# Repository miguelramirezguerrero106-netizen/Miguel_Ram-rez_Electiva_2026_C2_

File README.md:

# Miguel_Ram-rez_Electiva_2026_C2_
Entrega de trabajos para la asignatura de Electiva C2-2026

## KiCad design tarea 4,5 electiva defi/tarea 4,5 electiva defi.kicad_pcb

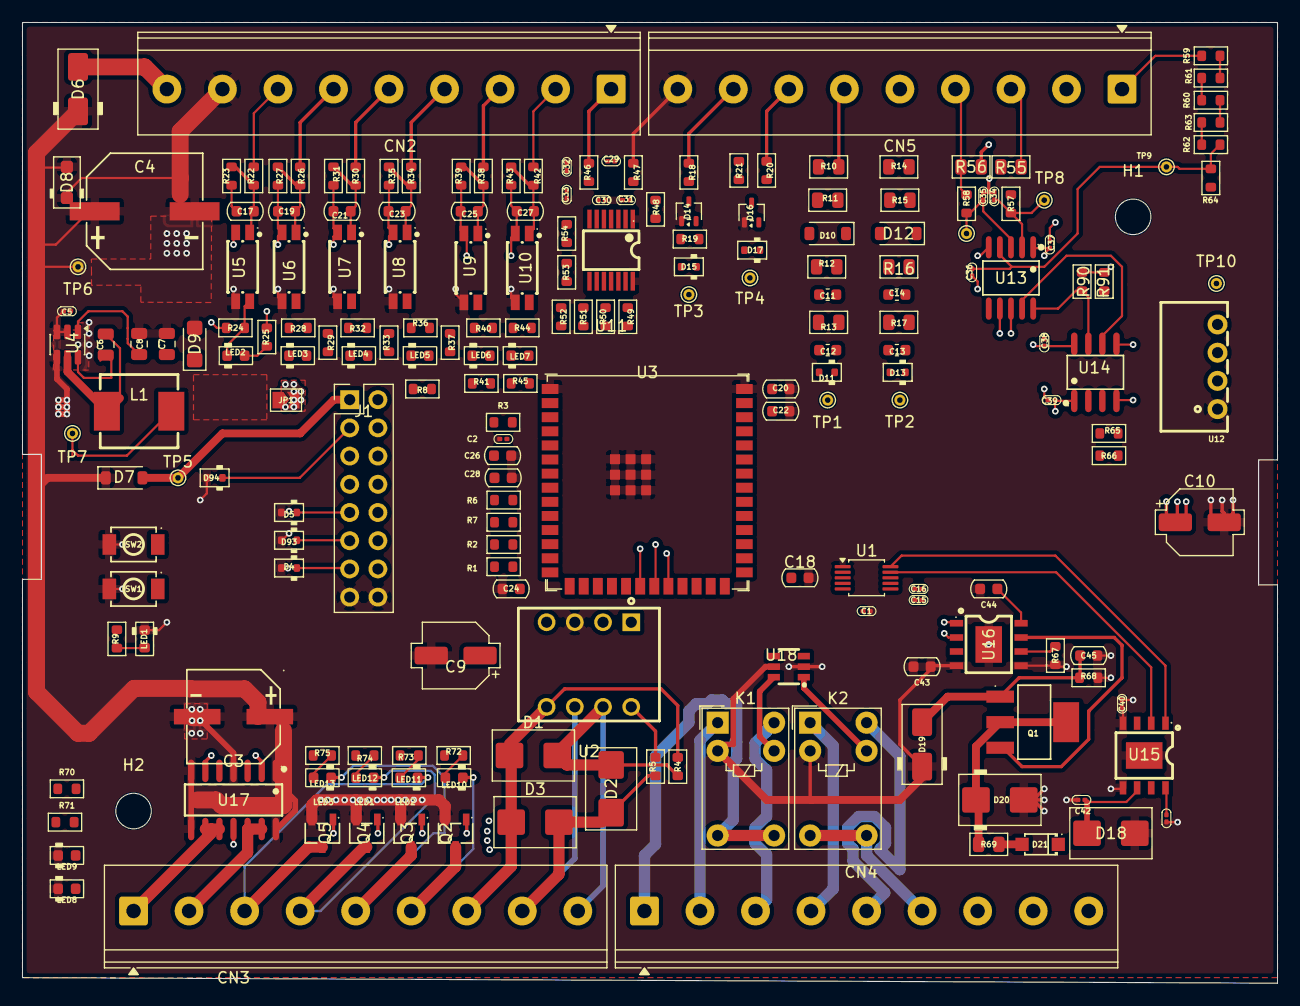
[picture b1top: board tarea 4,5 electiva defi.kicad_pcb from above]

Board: 4 copper layers, 113.0 x 86.5 mm, 205 parts (0 on the bottom side), 120 nets.

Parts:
C1, C2, C15, C16, C32, C33, C37, C38, C39: 100NF; C_0201_0603Metric
C3: 100uF; CAP-SMD_BD8.0-L8.3-W8.3-FD
C4: 220uF; CAP-SMD_BD10.0-L10.3-W10.3-LS11.3-FD
C5: 10uF; C_0201_0603Metric
C6: 100NF; C_0805_2012Metric
C7, C8: 22uF; C_0805_2012Metric
C9, C10: 47uF; CP_Elec_5x3
C11, C13: 100NF; C_0603_1608Metric
C12, C14: 47PF; C_0603_1608Metric
C17, C19, C21, C23, C25, C27: 2.2NF; C_0603_1608Metric
C18, C20, C22, C24, C26, C28: 1NF; C_0603_1608Metric
C29, C30: 0.01UF; C_0201_0603Metric
C31: 0.01; C_0201_0603Metric
C34, C35: 33NF; C_0201_0603Metric
C36: 68NF; C_0201_0603Metric
C40, C41, C42: C_0201; C_0201_0603Metric
C43, C44: C_0603; C_0603_1608Metric
C45: 1uF; C_0603_1608Metric
CN2, CN3, CN4, CN5: DB128V-5.08-9P-GN-S; TerminalBlock_Phoenix_PT-1,5-9-5.0-H_1x09_P5.00mm_Horizontal
D1, D3: SMBJ6.5CA; D_SMB_TVS
D2, D18: SMBJ12CA; D_SMB_TVS
D4, D5, D93, D94: ESD5Z3.3T; D_SOD-523
D6: MBRA340T; D_SMA
D7, D10, D12: 1N5819HW-7-F; D_SOD-123
D8: SMF24CA; D_SOD-123F
D9: SMF3.3; D_SMF
D11, D13, D15, D17: PESD5Z3.3; D_SOD-523
D14, D16: BAT54SW; SOT-323_SC-70
D19: SMAJ12A; D_SMA
D20: SMBJ28A; D_SMB
D21: DSK120_C22466355; SOD-123FL_L2.7-W1.8-LS3.8-RD
H1, H2: MountingHole; MountingHole_3.2mm_M3
J1: Conn_02x08_Odd_Even; PinHeader_2x08_P2.54mm_Vertical
JP1: SolderJumper_2_Open; SolderJumper-2_P1.3mm_Open_TrianglePad1.0x1.5mm
K1, K2: G5V-1; Relay_SPDT_Omron_G5V-1
L1: APH0630T4R7M; IND-SMD_L7.0-W6.6_APH0630
LED1, LED2, LED3, LED4, LED5, LED6, LED7, LED8, LED9, LED10, LED11, LED12, LED13: LED_0603; LED_0603_1608Metric
Q1: NCE60P04R; SOT-223-3_L6.5-W3.4-P2.30-LS7.0-BR
Q2, Q3, Q4, Q5: ZXMS6004FFTA; SOT-23-3_L2.9-W1.6-P1.90-LS2.8-BR
R1, R2: 10K; R_0603_1608Metric
R3, R4, R5, R57, R58: 1K; R_0603_1608Metric
R6, R7, R8, R46, R47: 0R; R_0603_1608Metric
R9: 2.2k; R_0603_1608Metric
R10, R14: 49.9R; R_0805_2012Metric
R11, R15: 120R; R_0805_2012Metric
R12, R16: 47K; R_0805_2012Metric
R13, R17: 100K; R_0805_2012Metric
R18, R20: 2.2K; R_0603_1608Metric
R19, R21: 1.05K; R_0603_1608Metric
R22, R26, R30, R34, R38, R42: 3.6K; R_0603_1608Metric
R23, R27, R31, R35, R39, R43: 3.3K; R_0603_1608Metric
R24, R28, R32, R36, R40, R44: 22K; R_0603_1608Metric
R25, R29, R33, R37, R41, R45, R67, R70, R71, R72, R73, R74, R75: R_0603; R_0603_1608Metric
R48: 20K; R_0603_1608Metric
R49, R50, R51, R52, R53, R54: 150; R_0603_1608Metric
R55, R56: 0.51; R_0805_2012Metric
R59, R60, R61, R62, R63: 390K; R_0603_1608Metric
R64: 510; R_0603_1608Metric
R65, R66, R90, R91: 4.7K; R_0603_1608Metric
R68: 470K; R_0603_1608Metric
R69: 15R; R_0805_2012Metric
SW1, SW2: TS-1088-AR02016; SW-SMD_L3.9-W3.0-P4.45
TP1, TP2, TP3, TP4: TestPoint_Hole1; TestPoint_THTPad_D1.0mm_Drill0.5mm
TP5, TP6, TP7, TP8, TP9, TP10, TP11: TestPoint; TestPoint_THTPad_D1.0mm_Drill0.5mm
U1: ADS1115IDGS; TSSOP-10_3x3mm_P0.5mm
U2: TD301M485_C5451847; COMM-TH_TD301M485
U3: ESP32-S3-WROOM-1; ESP32-S3-WROOM-1U
U4: AP63203WU; TSOT-23-6
U5, U6, U7, U8, U9, U10: AT3H4B-CUH-S; SSOP-4_L2.7-W4.6-P1.27-LS7.0-TL
U11: MAX31856MUD+; TSSOP-14_L5.0-W4.4-P0.65-LS6.4-BL
U12: B0303S-1WR3_C7465185; PWRM-TH_BXXXXS-1WR3
U13: BL0942; SSOP-10_L4.9-W3.9-P1.00-LS6.0-BL
U14: ISO7021DR; SOIC-8_L4.9-W3.9-P1.27-LS6.0-BL
U15: GP8211S-TC50-EW; ESOP-8_L4.9-W3.9-P1.27-LS6.0-BL-EP
U16: GP8302-TC50-EW; ESOP-8_L4.9-W3.9-P1.27-LS6.0-BL-EP
U17: BTS723GWXUMA1; SOIC-14_L8.7-W3.9-P1.27-LS6.0-BL
U18: LK1802; SOT-23-6_L2.9-W1.6-P0.95-LS2.8-BR

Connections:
+3.3V: C1.1, C9.1, C10.1, C32.1, C33.1, C39.1, D14.2 (K), D16.2 (K), J1.2, JP1.2 (B), R1.1, R2.1, R3.1, R8.1, R24.2, R25.1, R28.2, R29.1, R32.2, R33.1, R36.2, R37.1, R40.2, R41.1, R44.2, R45.1, R65.2, R66.2, R72.1, R73.1, R74.1, R75.1, U1.8 (VDD), U2.4 (VCC), U3.2 (3V3), U11.5 (AVDD), U11.8 (DVDD), U12.2 (+Vin), U14.1 (VCC1), U17.11 (SPU)
+5V: D7.2 (A), J1.1, TP5.1 (1_1)
/PowerSupply/ps_out: C7.1, C8.1, D9.1 (A1), JP1.1 (A), L1.2, TP7.1 (1_1), U4.1 (FB)
/control/CON_IN_0-10V_1: CN3.7, CN3.8
/control/CON_IN_4-20MA_1: CN3.5, CN3.6
/control/CON_RS485_A: CN4.9, R5.1, U2.7 (B)
/control/CON_RS485_B: CN4.8, D2.2 (A), D3.2 (A), R4.2, U2.6 (A)
/control/CON_RS485_G: CN4.7, D1.2 (A), D3.1 (K), R5.2, U2.5 (RGND)
/control/EN: C2.2, R3.2, U3.3 (EN)
/control/EnergyMeterA1/CT_N: R56.2, R58.1
/control/EnergyMeterA1/CT_P: R55.1, R57.1
/control/EnergyMeterA1/RX: R65.1, U14.3 (INB)
/control/EnergyMeterA1/TX: R66.1, U14.2 (OUTA)
/control/I2C_SCK: J1.10, U1.10 (SCL), U3.11 (GPIO18/U1RXD/ADC2_CH7/CLK_OUT3)
/control/I2C_SDA: J1.8, U1.9 (SDA), U3.10 (GPIO17/U1TXD/ADC2_CH6)
/control/IN-0-10V1/COM: C16.2, D17.2 (A), R21.2
/control/IN-0-10V1/OUT3V: C16.1, D16.3 (COM), D17.1 (K), R20.2, R21.1
/control/IN-0-10V/COM: C15.2, D15.2 (A), R19.2
/control/IN-0-10V/OUT3V: C15.1, D14.3 (COM), D15.1 (K), R18.2, R19.1
/control/IN-4-20MA1/IN_N: C13.2, C14.2, D12.2 (A), D13.2 (A), R15.1
/control/IN-4-20MA1/OUT: C14.1, D13.1 (K), R17.1
/control/IN-4-20MA/IN_N: C11.2, C12.2, D10.2 (A), D11.2 (A), R11.1
/control/IN-4-20MA/OUT: C12.1, D11.1 (K), R13.1
/control/IN-DI1/COM: C19.2, R27.1, U6.2 (CAT/AN)
/control/IN-DI1/OUT: C20.1, LED3.1 (K), R28.1, U6.4 (COL)
/control/IN-DI2/COM: C21.2, R31.1, U7.2 (CAT/AN)
/control/IN-DI2/OUT: C22.1, LED4.1 (K), R32.1, U7.4 (COL)
/control/IN-DI3/COM: C23.2, R35.1, U8.2 (CAT/AN)
/control/IN-DI3/OUT: C24.1, LED5.1 (K), R36.1, U8.4 (COL)
/control/IN-DI4/COM: C25.2, R39.1, U9.2 (CAT/AN)
/control/IN-DI4/OUT: C26.1, LED6.1 (K), R40.1, U9.4 (COL)
/control/IN-DI5/COM: C27.2, R43.1, U10.2 (CAT/AN)
/control/IN-DI5/OUT: C28.1, LED7.1 (K), R44.1, U10.4 (COL)
/control/IN-DI/COM: C17.2, R23.1, U5.2 (CAT/AN)
/control/IN-DI/OUT: C18.1, LED2.1 (K), R24.1, U5.4 (COL)
/control/IN_NPN1: CN4.3, CN4.4, CN4.5, CN4.6, SW1.2, SW2.2, TP1.1 (1_1), TP2.1 (1_1), U1.4 (AIN0), U1.5 (AIN1), U3.15 (GPIO3/TOUCH3/ADC1_CH2), U3.16 (GPIO46), U3.24 (GPIO47/SPICLK_P/SUBSPICLK_P_DIFF), U3.27 (GPIO0/BOOT), U3.38 (GPIO2/TOUCH2/ADC1_CH1), U3.39 (GPIO1/TOUCH1/ADC1_CH0)
/control/LCD_CS: J1.7, U3.35 (MTMS/GPIO42)
/control/LCD_EN: J1.4, R8.2
/control/LED_INFO: R9.1, U3.26 (GPIO45)
/control/OUT3V: TP3.1 (1_1), TP4.1 (1_1), U1.6 (AIN2), U1.7 (AIN3)
/control/OUT-0-10V/OUT-0-10V: C42.1, D18.2 (A), U15.6 (VOUT)
/control/OUT-NPN1/OUT: LED11.1 (K), Q3.3 (D)
/control/OUT-NPN2/OUT: LED12.1 (K), Q4.3 (D)
/control/OUT-NPN3/OUT: LED13.1 (K), Q5.3 (D)
/control/OUT-NPN/OUT: LED10.1 (K), Q2.3 (D)
/control/OUT-PNP/out1: R70.1, U17.9 (OUT2), U17.10 (OUT2)
/control/OUT-PNP/out2: R71.1, U17.12 (OUT1), U17.13 (OUT1)
/control/OUT_NPN1: CN2.2, CN2.3, CN2.4, CN2.5, CN2.6, CN2.7, U3.4 (GPIO4/TOUCH4/ADC1_CH3), U3.5 (GPIO5/TOUCH5/ADC1_CH4), U3.6 (GPIO6/TOUCH6/ADC1_CH5), U3.7 (GPIO7/TOUCH7/ADC1_CH6)
/control/RESET: J1.5, U3.22 (GPIO14/TOUCH14/ADC2_CH3/FSPIWP/FSPIDQS/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)
/control/RLY/RLY2_COM: K1.5, K1.6
/control/RS485-RX: R2.2, U2.1 (RXD), U3.12 (GPIO8/TOUCH8/ADC1_CH7/SUBSPICS1)
/control/RS485-TX: R1.2, U2.2 (TXD), U3.17 (GPIO9/TOUCH9/ADC1_CH8/FSPIHD/SUBSPIHD)
/control/SD_CS: D94.1 (K), J1.3, U3.18 (GPIO10/TOUCH10/ADC1_CH9/FSPICS0/FSPIIO4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)
/control/SPI_CLK: D4.1 (K), J1.13, U3.20 (GPIO12/TOUCH12/ADC2_CH1/FSPICLK/FSPIIO6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)
/control/SPI_MISO: D5.1 (K), J1.9, U3.21 (GPIO13/TOUCH13/ADC2_CH2/FSPIQ/FSPIIO7/S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)
/control/SPI_MOSI: D93.1 (K), J1.11, U3.19 (GPIO11/TOUCH11/ADC2_CH0/FSPID/FSPIIO5/S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)
/control/ST1_ST2: R6.1, R7.1, U3.32 (MTCK/GPIO39/CLK_OUT3/SUBSPICS1)
/control/TC/TC-: R47.1, R48.1
/control/TP_INT: J1.6, U3.33 (MTDO/GPIO40/CLK_OUT2)
/control/USB+: J1.14, U3.14 (GPIO20/U1CTS/ADC2_CH9/CLK_OUT1/USB_D+)
/control/USB-: J1.12, U3.13 (GPIO19/U1RTS/ADC2_CH8/CLK_OUT2/USB_D-)
Earth: C36.2, C37.2, C38.2, CN3.2, R55.2, R56.1, R64.1, U12.3 (-Vout), U13.5 (GND), U13.7 (SEL), U14.5 (GND2)
GND: C1.2, C2.1, C3.1, C3.2, C4.1, C4.2, C5.1, C5.2, C7.2, C8.2, C9.2, C10.2, C18.2, C20.2, C22.2, C24.2, C26.2, C28.2, C30.2, C31.2, C32.2, C33.2, C39.2, C40.1, C40.2, C41.2, C42.2, C43.1, C43.2, C44.2, C45.2, CN2.8, CN5.9, D4.2 (A), D5.2 (A), D6.1 (K), D7.1 (K), D8.1 (K), D8.2 (A), D9.2 (A2), D14.1 (A), D16.1 (A), D18.1 (K), D19.1 (K), D20.2 (A), D93.2 (A), D94.2 (A), J1.15, J1.16, K1.2, K2.2, LED1.1 (K), LED8.1 (K), LED9.1 (K), Q2.2 (S), Q3.2 (S), Q4.2 (S), Q5.2 (S), R67.2, R68.2, SW1.1, SW2.1, TP6.1 (1_1), U1.1 (ADDR), U1.3 (GND), U2.3 (GND), U3.1 (GND), U3.40 (GND), U3.41 (GND), U4.2 (EN), U4.3 (IN), U4.4 (GND), U5.3 (EM), U6.3 (EM), U7.3 (EM), U8.3 (EM), U9.3 (EM), U10.3 (EM), U11.1 (AGND), U11.14 (DGND), U12.1 (-Vin), U15.4 (VCC), U15.5 (GND), U15.9 (EP), U16.4 (VCC), U16.5 (GND), U16.9 (EP), U17.1 (VBB), U17.4 (GND), U17.7 (VBB), U17.8 (VBB), U17.14 (VBB), U18.2 (E), U18.5 (COM)
unnamed: C11.1, R12.1, R13.2
unnamed: C13.1, R16.1, R17.2
unnamed: C34.2, C35.1
unnamed: D1.1 (K), D2.1 (K)
unnamed: D10.1 (K), R10.1, R11.2, R12.2
unnamed: D12.1 (K), R14.1, R15.2, R16.2
unnamed: C45.1, D19.2 (A), Q1.1 (G), R68.1
unnamed: D20.1 (K), Q1.2 (D), Q1.4 (D), R69.1
unnamed: D21.2 (A), R69.2
unnamed: K2.5, K2.6
unnamed: LED1.2 (A), R9.2
unnamed: LED2.2 (A), R25.2
unnamed: LED3.2 (A), R29.2
unnamed: LED4.2 (A), R33.2
unnamed: LED5.2 (A), R37.2
unnamed: LED6.2 (A), R41.2
unnamed: LED7.2 (A), R45.2
unnamed: LED8.2 (A), R70.2
unnamed: LED9.2 (A), R71.2
unnamed: LED10.2 (A), R72.2
unnamed: LED11.2 (A), R73.2
unnamed: LED12.2 (A), R74.2
unnamed: LED13.2 (A), R75.2
unnamed: Q1.3 (S), U16.7 (IOUT)
unnamed: R59.2, R60.1
unnamed: R60.2, R61.1
unnamed: R61.2, R62.1
unnamed: R62.2, R63.1
unnamed: R4.1, U2.8 (VO)
unnamed: C6.1, U4.6 (BST)
unnamed: C6.2, L1.1, U4.5 (SW)
unnamed: C17.1, R22.2, R23.2, U5.1 (AN/CAT)
unnamed: C19.1, R26.2, R27.2, U6.1 (AN/CAT)
unnamed: C21.1, R30.2, R31.2, U7.1 (AN/CAT)
unnamed: C23.1, R34.2, R35.2, U8.1 (AN/CAT)
unnamed: C25.1, R38.2, R39.2, U9.1 (AN/CAT)
unnamed: C27.1, R42.2, R43.2, U10.1 (AN/CAT)
unnamed: R48.2, U11.2 (BIAS)
unnamed: R53.1, U11.10 (SCK)
unnamed: R51.1, U11.12 (SDI)
unnamed: R52.1, U11.11 (SDO)
unnamed: C29.2, C30.1, R46.2, U11.4 (T+)
unnamed: C29.1, C31.1, R47.2, U11.3 (T-)
unnamed: R54.1, U11.9 (~CS)
unnamed: R49.1, U11.7 (~DRDY)
unnamed: R50.1, U11.13 (~FAULT)
unnamed: C35.2, R58.2, TP11.1 (1_1), U13.3 (IN)
unnamed: C34.1, R57.2, TP8.1 (1_1), U13.2 (IP)
unnamed: R90.1, U13.9 (RX/SDI), U14.6 (OUTB)
unnamed: R91.1, U13.10 (TX/SDO), U14.7 (INA)
unnamed: C36.1, R63.2, R64.2, TP9.1 (1_1), U13.4 (VP)
unnamed: C41.1, U15.8 (V5V)
unnamed: R67.1, U16.6 (SET)
unnamed: C44.1, U16.8 (V5V)
unnamed: K1.9, U18.1 (1C)
unnamed: K2.9, U18.6 (2C)
VCC: C37.1, C38.1, R90.2, R91.2, TP10.1 (1_1), U12.4 (+Vout), U13.1 (VDD), U13.8 (SCLK_BPS), U14.8 (VCC2)

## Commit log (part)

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2026-05-21 Add files via upload
    Tarea 1
2026-06-11 Tarea 1
    Parte superior del case PLC de la asignatura electiva mecatrónica
2026-06-11 Create Tarea 2
2026-06-11 Create parte superior plc electiva
2026-06-11 Tarea 2
    Diseño CAD del case del proyecto PLC para la asignatura de electiva
2026-06-11 Rename Ensayo MBSE.pdf to Tarea 1_Ensayo MBSE.pdf
2026-06-11 Hoja de notas
2026-06-11 Parte inferior case para el diseño de PLC electiva
2026-06-17 Dibujo hecho en clase del case y pinout del PLC
